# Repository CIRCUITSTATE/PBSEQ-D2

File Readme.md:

# PBSEQ-D2

**PBSEQ-D2** is a simple push-button based power sequencer demo board designed in KiCad. You can press the push-button momentarily to turn on the output. Pressing again will turn off the output. A PMOS transistor is used as a high-side switch to control the power. An NMOS transistor controls the power sequencing. This demo project is fully open-source and you can find the source design files here.

A tutorial of designing and testing the circuit will soon be available at [CIRCUITSTATE](https://www.circuitstate.com/).

## Project Details

- **Parent Project:** PBSEQ
- **Variant Name:** PBSEQ-D2
- **Latest Revision:** `R0.1`
- **EDA Tools:** KiCad V8
- **Layer Count:** 2
- **Board Thickness:** 1.6 mm
- **Dimensions:** 19 x 19 mm

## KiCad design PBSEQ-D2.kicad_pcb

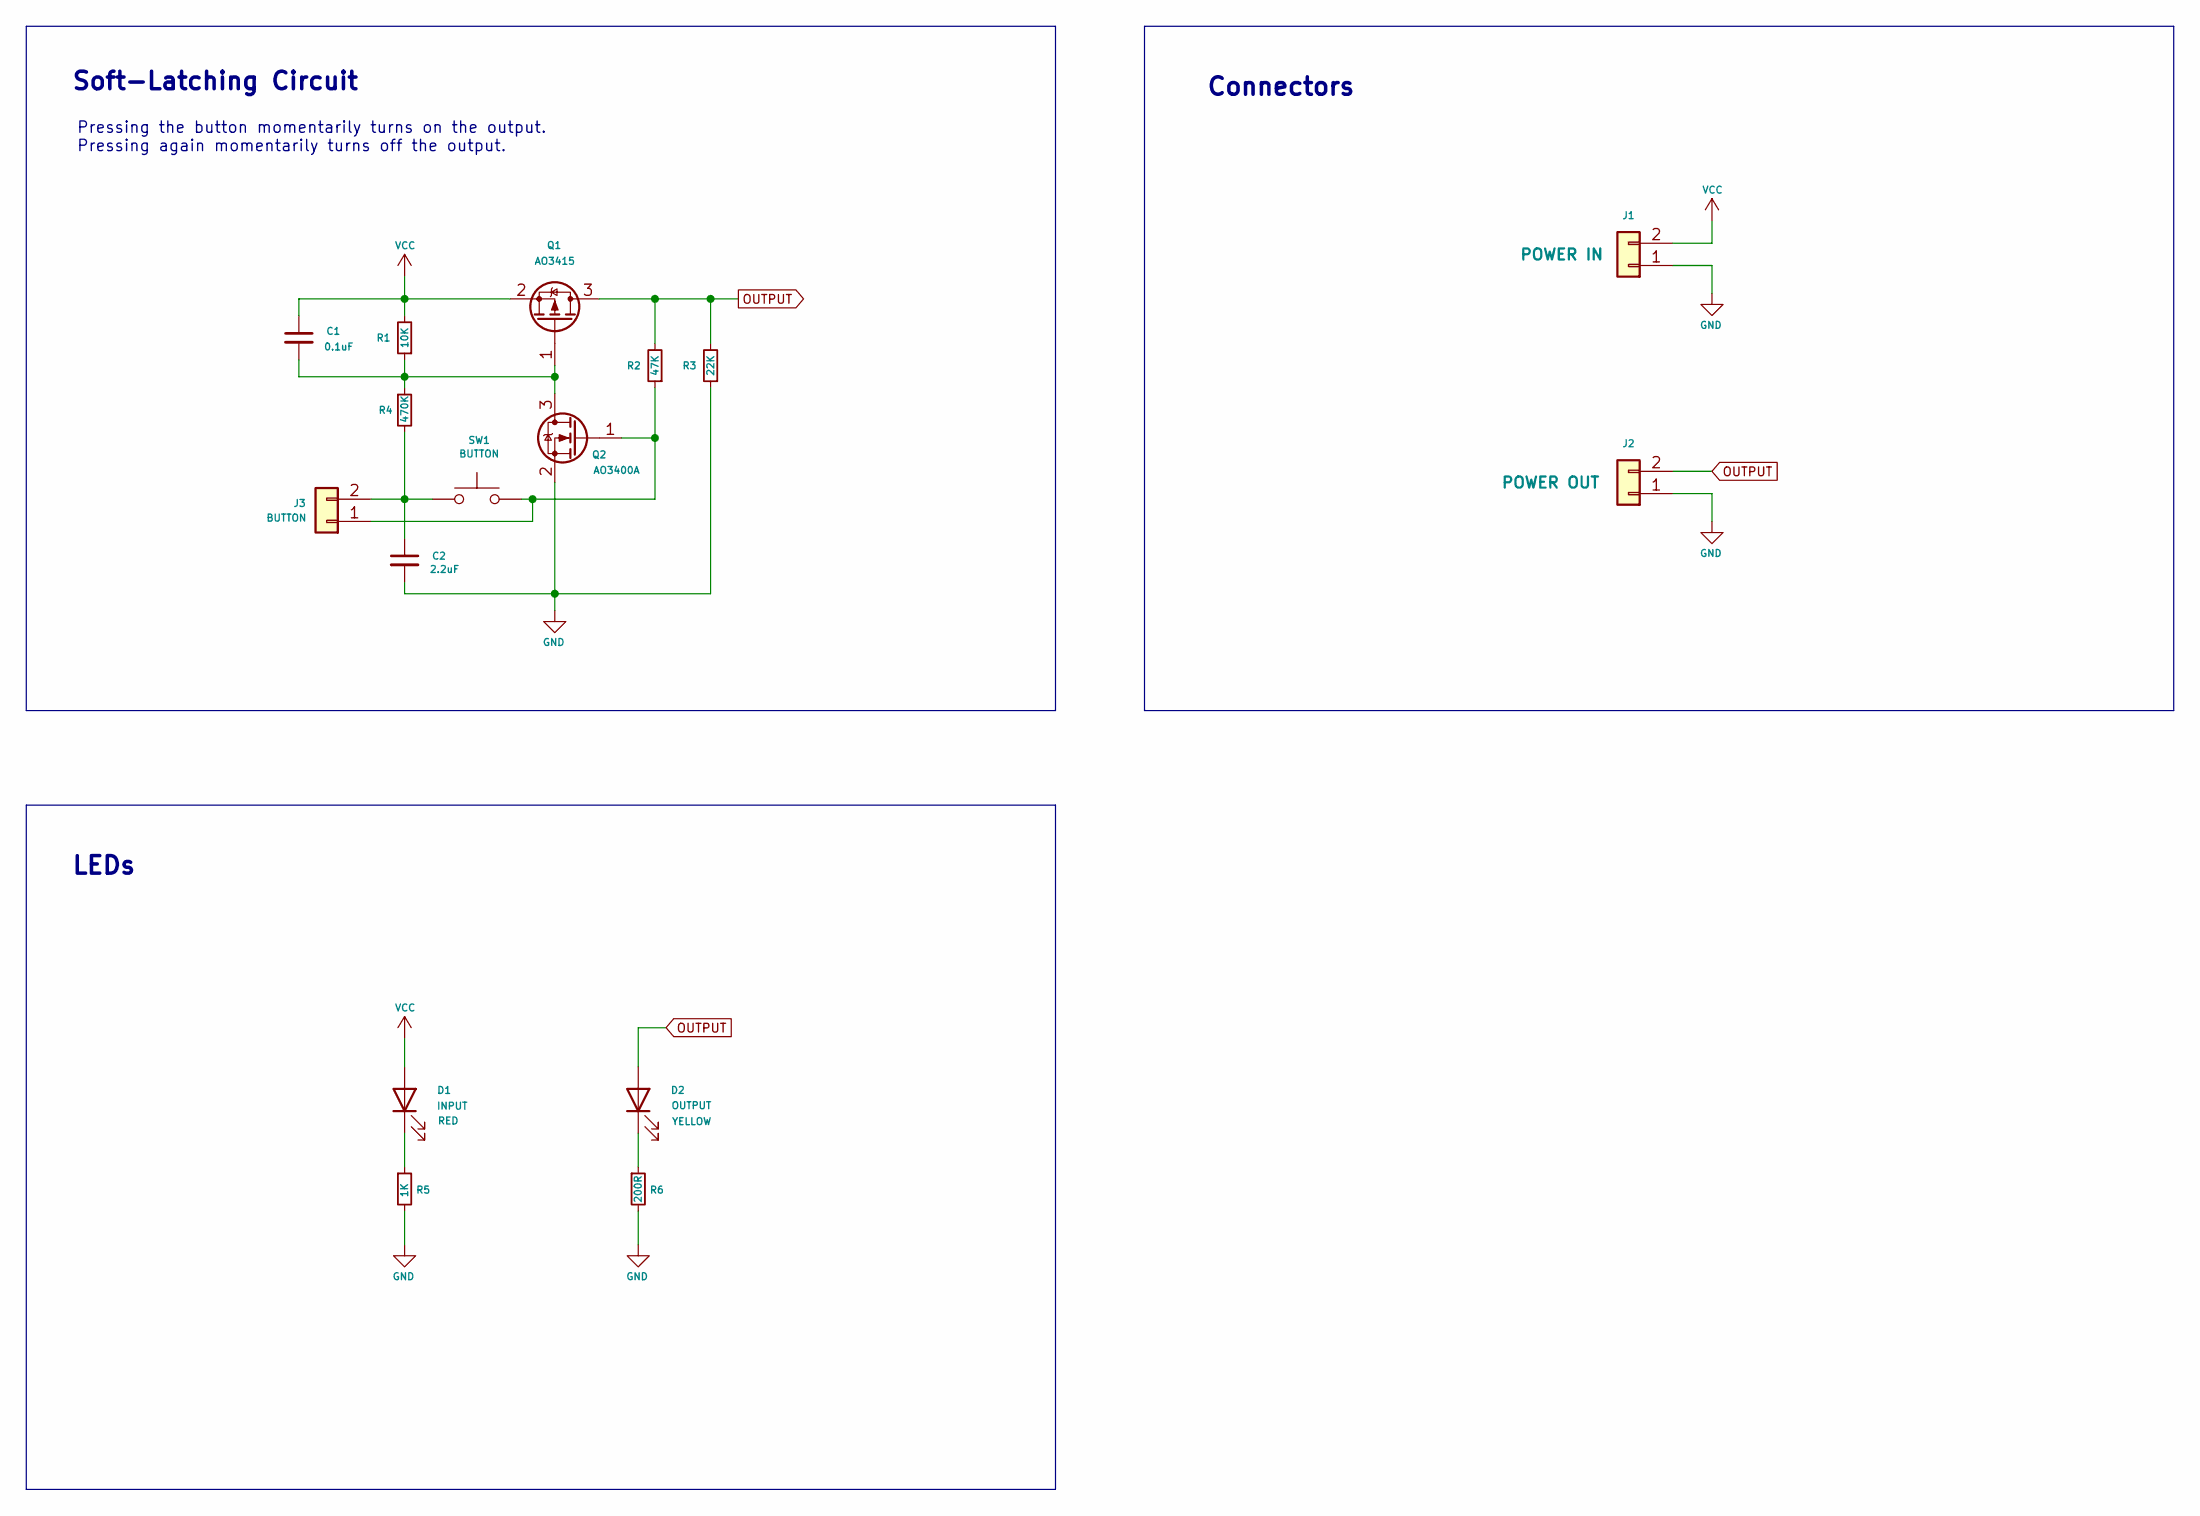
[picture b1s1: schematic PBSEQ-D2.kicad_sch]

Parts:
C1: 0.1uF; C_0603_1608Metric; MPN 0603B104J500CT
C2: 2.2uF; C_0603_1608Metric; MPN CL10A225KA8NNNC
D1: RED; LED_0603_1608Metric; MPN 19-21SURC/S530-A2/TR8
D2: YELLOW; LED_0603_1608Metric; MPN 19-213/Y2C-FN2P2VZ/3T
J1: POWER IN; PinHeader_1x02_P2.54mm_Vertical; MPN DNP
J2: POWER OUT; PinHeader_1x02_P2.54mm_Vertical; MPN DNP
J3: BUTTON; PinHeader_1x02_P2.54mm_Vertical; MPN DNP
Q1: AO3415; SOT-23; MPN AO3415
Q2: AO3400A; SOT-23; MPN AO3400A
R1: 10K; R_0603_1608Metric; MPN WR06X1002FTL
R2: 47K; R_0603_1608Metric; MPN WR06X4702FTL
R3: 22K; R_0603_1608Metric; MPN WR06X2202FTL
R4: 470K; R_0603_1608Metric; MPN WR06X4703FTL
R5: 1K; R_0603_1608Metric; MPN WR06X1001FTL
R6: 200R; R_0603_1608Metric; MPN WR06X2000FTL
SW1: BUTTON; CK_SW_SPST_UK-B0273-SP25Y; MPN TS-1088R-02526

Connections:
GND: C2.2, J1.1, J2.1, Q2.2 (S), R3.1, R5.2, R6.2
unnamed: D1.1 (K), R5.1
unnamed: D2.1 (K), R6.1
unnamed: J3.1, Q2.1 (G), R2.1, SW1.2
unnamed: C2.1, J3.2, R4.2, SW1.1
unnamed: C1.2, Q1.1 (G), Q2.3 (D), R1.1, R4.1
OUTPUT: D2.2 (A), J2.2, Q1.3 (D), R2.2, R3.2
VCC: C1.1, D1.2 (A), J1.2, Q1.2 (S), R1.2

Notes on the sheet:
Soft-Latching Circuit
LEDs
Connectors
Pressing the button momentarily turns on the output. Pressing again momentarily turns off the output.

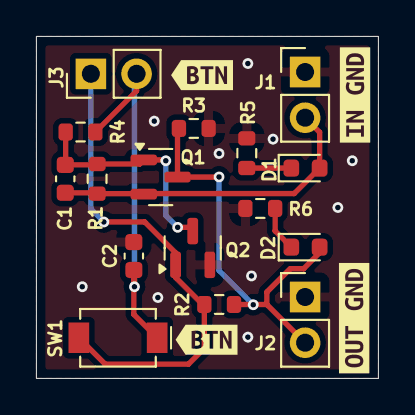
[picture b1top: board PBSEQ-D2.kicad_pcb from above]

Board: 2 copper layers, 19.0 x 19.0 mm, 21 parts (1 on the bottom side), 8 nets.

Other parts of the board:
kibuzzard-663FBC0C, kibuzzard-663FBC0C#2: G***; kibuzzard-663FBC0C
kibuzzard-663FBCF2: G***; kibuzzard-663FBCF2
kibuzzard-663FBD0F: G***; kibuzzard-663FBD0F
kibuzzard-66404F66: G***; kibuzzard-66404F66

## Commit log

2024-05-12 R0.1 Init Commit
    * Routing completed.
    * DRC passes.
    * Generated manufacturing files.
    * Added Changes and Readme.
    * New Revision `R0.1`.
2024-05-12 Updated Drill/Place origin
2024-05-18 Exported images
    * Updated Readme. Added images.
2024-08-01 Updated resistor values
    * Updated values of `R1` and `R4`. The new values are found to be working with practical testing.
    * Updated `Q1` value to `AO3415` based on testing.
    * Added net classes and highlights.
    * Updated BoM.
    * Imported new changes to the PCB.
    * No changes in the electrical design.
2024-08-21 Exported schematic
    * Added net highlights on the PCB.
    * Exported schematic file. There are no other changes to the schematic or PCB.
